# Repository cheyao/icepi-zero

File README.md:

# Icepi Zero - The portable FPGA development board

| Get your own at: | [**Crowd Supply**](https://www.crowdsupply.com/icy-electronics/icepi-zero) | [**Elecrow**](https://www.elecrow.com/icepi-zero.html) | [**Mouser Electronics**](https://eu.mouser.com/en/ProductDetail/Icy-Electronics/ICEPI-ZERO-QTY-1) |
| ---------------- | ------------------------ | ------------------ | --------- |

If you are a student/educational institute, send me an email at `cyao _at_ duck.com` and get a discount to buy an Icepi Zero at just $65 (shipping exclusive).

We also got a [Discord server](https://discord.gg/vzrqfhcvWr)! Feel free to ask any questions here.

## What is the Icepi Zero?

The Icepi Zero is an FPGA development board in the popular Raspberry Pi Zero form factor. It carries a Lattice ECP5 25F, enabling powerful designs while keeping a small portable size. It also has a GPDI mini (General Purpose Display Interface, same as the one on the Pi Zero) port allowing easy digital video output.

## Why Icepi Zero?

Currently most powerful FPGA boards on the market are expensive and bulky.

I've always wanted a low-cost portable FPGA with video output to make my own CPU, but there isn't any on the market.

The Icepi Zero aims to fix this. Carrying a powerful ECP5 FPGA on a small Raspberry Pi Zero form factor, it is the ultimate portable solution for FPGA development. Additionally packing a GPDI mini port and 3 USB-C ports, it allows interfacing with multiple external I/O devices.

Icepi Zero is for everyone: Students can use it to learn about the internals of modern processors. Gamers can use it to emulate old hardware. Programmers can use it to test their code on multiple architectures.

<sub>Oberon running on Icepi Zero</sub>

Icepi Zero also has an on-board USB to JTAG converter, so no external programmers are needed.

Moreover Icepi Zero is fully open-source, no strings attached. Learn from the design! ([OSHWA cerified FR000026](https://certification.oshwa.org/fr000026.html)).

## Features

- Raspberry Pi Zero form factor
- Lattice ECP5U FPGA:
    - 24k LUT
    - 112 KiB of RAM
- One MiniGPDI connector (it's HDM- but I don't have the money to buy a license...)
- Three USB-C Ports
- 256Mbit 166MHz SDRAM
- MicroSD card slot
- On-board USB to JTAG and UART converter
- 50MHz external oscillator
- 128 Mbit of flash
- 4 user LEDs
- 2 user buttons

This powerful configuration allows the PCB to be used in numerous ways, including real time video processing, hardware AI acceleration and prototyping of ASICs. 

## Emulation

Over the course of multiple weeks, multiple emulation cores have been ported over, such as the [Oberon](https://github.com/cheyao/oberon), [Apple I](https://github.com/cheyao/apple-one) and the [Acorn Atom](https://github.com/cheyao/acorn_atom)! The Icepi Zero allows you to take cycle accurate replicas of your favourite systems in your pocket.

<sub>Apple I running on the Icepi</sub>

<sub>Acorn Atom running on the Icepi</sub>

## Learning

It is also supported by icestudio (custom fork: https://github.com/cheyao/icestudio), allowing easy access for beginners.

## Usage

Check out the `gateware` folder for example code and compilation instructions!

If you want to order this board, it uses a 1.2mm/1.6mm PCB with JLC04121H-7628 Stackup. Gerbers are in the `production` folder in the `hardware` directory.

For the PCB, the smallest component size is 0201 for 27 Ohm resistors on the USB-C datalines. But if you want only 0402 components, just delete those 0201 resistors and you will be fine.

NOTE: If you fabbed v1.1 before 01/06, the pins of the USB pullups and LED0 is different - check your gerbers.

[View PCB online](https://kicanvas.org/?github=https%3A%2F%2Fgithub.com%2Fcheyao%2Ficepi-zero%2Ftree%2Fmain%2Fhardware%2Fv1.2)

## Acknowledgments

This project was inspired by the [ulx3s](https://github.com/emard/ulx3s), huge props to the ulx3s team for making such a good board!

## Contact

If there is any questions DM `cyao.` or join the [discord server](https://discord.gg/vzrqfhcvWr)! Feel free to ask any questions here. Mail is also accepted at `cyao _at_ duck.com`. :)

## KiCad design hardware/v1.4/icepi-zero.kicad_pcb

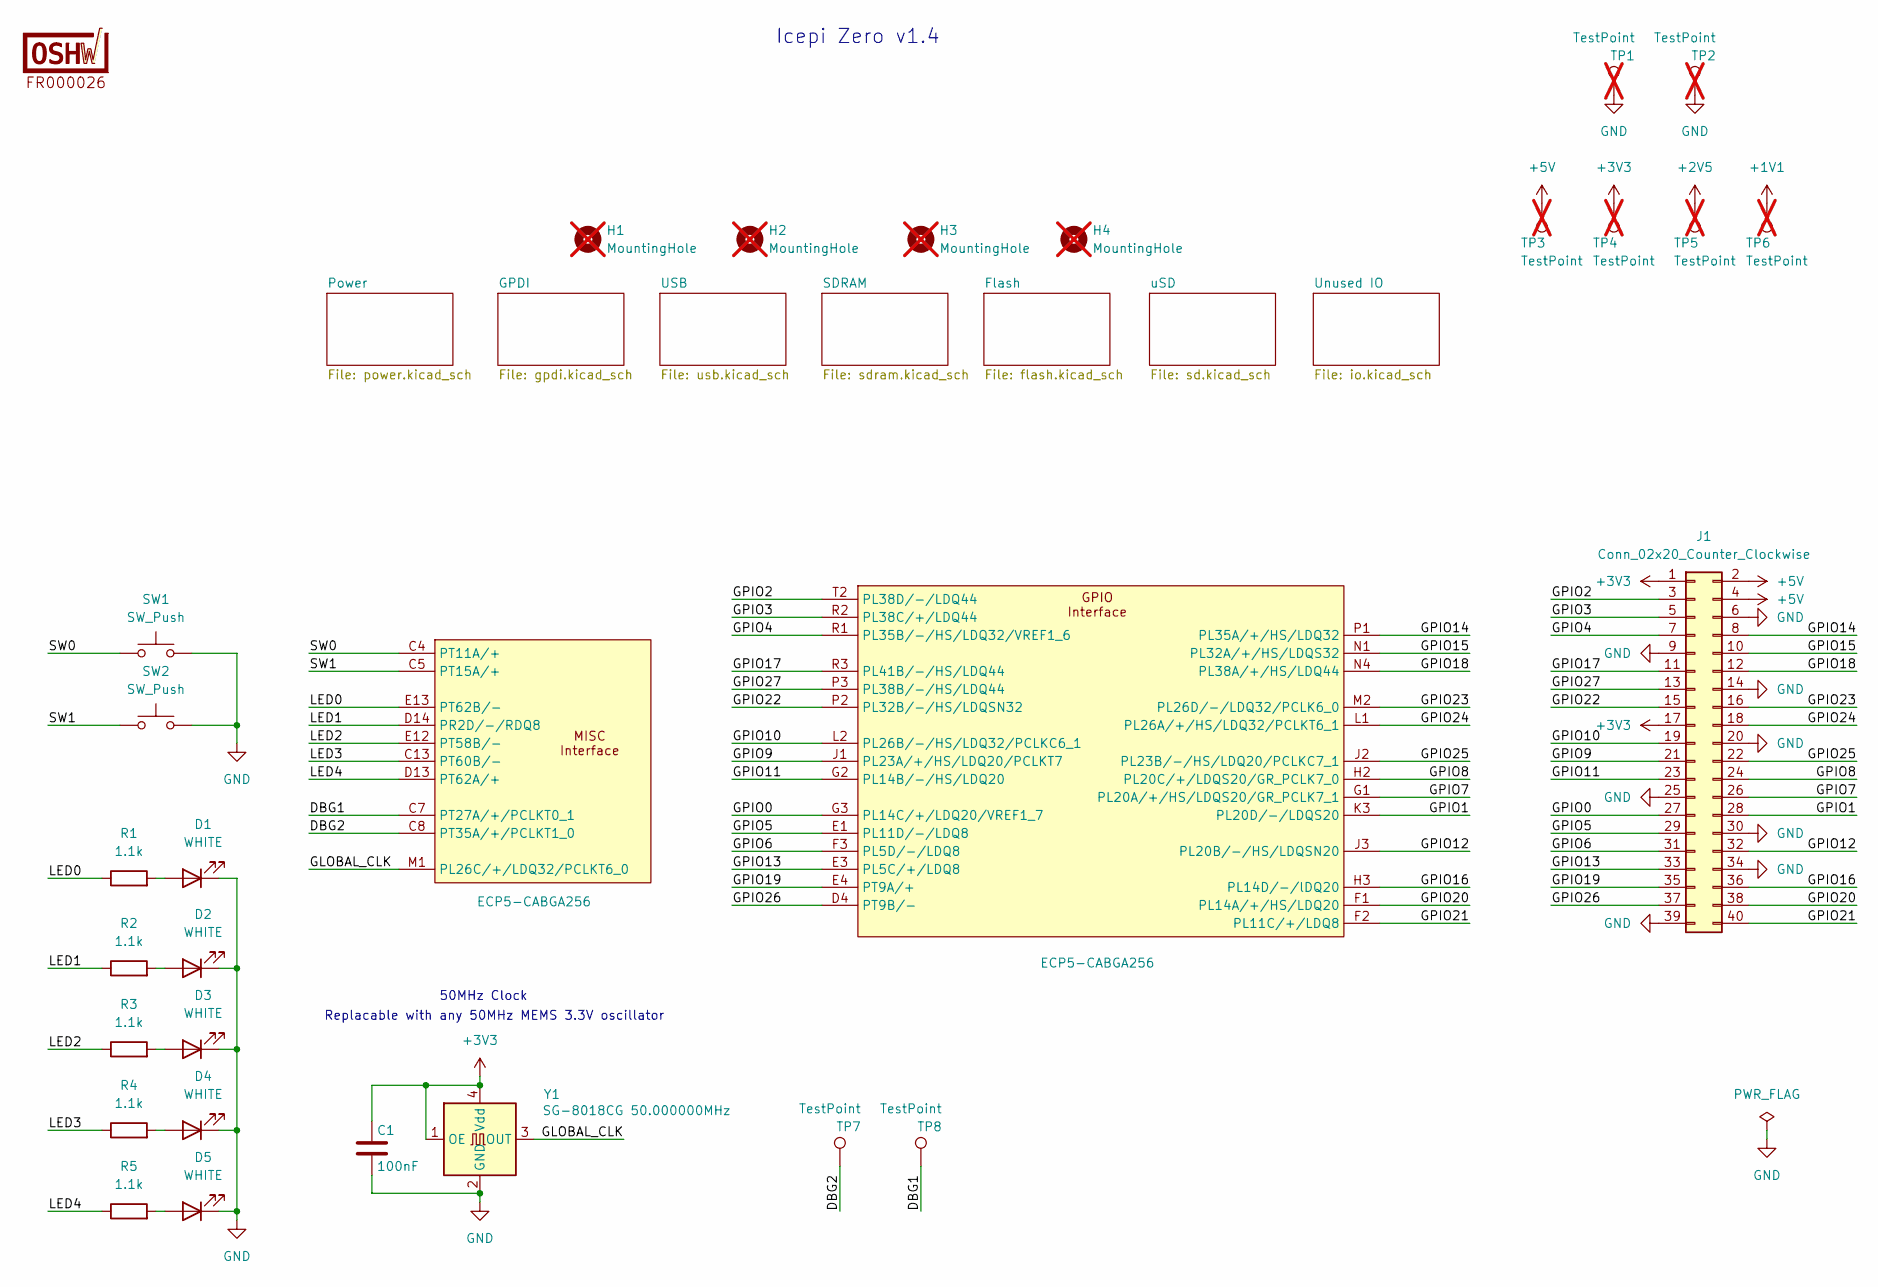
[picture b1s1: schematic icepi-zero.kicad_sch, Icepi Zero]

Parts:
C1: 100nF; C_0402_1005Metric; Manufactuer Part Number CL05B104KB54PNC; LCSC Part # C307331
D1, D2, D3, D4, D5: WHITE; LED_0603_1608Metric; Manufactuer Part Number KT-0603W; LCSC Part # C2290
H1, H2, H3, H4: MountingHole; MountingHole_2.7mm_M2.5; not fitted
J1: Conn_02x20_Counter_Clockwise; PinHeader_2x20_P2.54mm_Vertical
LOGO1: Icy Electronics Logo
R1, R2, R3, R4, R5: 1.1k; R_0402_1005Metric; Manufactuer Part Number 0402WGF1001TCE; LCSC Part # C140223
SW1, SW2: SW_Push; switch_button_TS-1088-AR02016; Manufactuer Part Number TS-1088-AR02016; LCSC Part # C720477
TP1, TP2, TP3, TP4, TP5, TP6: TestPoint; TestPoint_Pad_D2.0mm_Blank; not fitted
TP7, TP8: TestPoint; TestPoint_Pad_D1.0mm_Blank
U1: ECP5-CABGA256; BGA-256_14.0x14.0mm_Layout16x16_P0.8mm_Ball0.45mm_Pad0.32mm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; Manufactuer Part Number LFE5U-25F-6BG256C; LCSC Part # C1521614
Y1: SG-8018CG 50.000000MHz; Oscillator_SMD_SiT_PQFN-4Pin_2.5x2.0mm; Manufactuer Part Number SG-8018CG 50.000000MHz TJHSA; LCSC Part # C390526

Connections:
+1V1: TP6.1 (1_1); also elsewhere on the board
+2V5: TP5.1 (1_1); also elsewhere on the board
+3V3: C1.1, J1.1, J1.17, TP4.1 (1_1), Y1.1 (OE), Y1.4 (Vdd); also elsewhere on the board
+5V: J1.2, J1.4, TP3.1 (1_1); also elsewhere on the board
/DBG1: TP8.1 (1_1), U1.C7 (PT27A/+/PCLKT0_1)
/DBG2: TP7.1 (1_1), U1.C8 (PT35A/+/PCLKT1_0)
/GLOBAL_CLK: U1.M1 (PL26C/+/LDQ32/PCLKT6_0), Y1.3 (OUT)
/GPIO0: J1.27, U1.G3 (PL14C/+/LDQ20/VREF1_7)
/GPIO1: J1.28, U1.K3 (PL20D/-/LDQS20)
/GPIO2: J1.3, U1.T2 (PL38D/-/LDQ44)
/GPIO3: J1.5, U1.R2 (PL38C/+/LDQ44)
/GPIO4: J1.7, U1.R1 (PL35B/-/HS/LDQ32/VREF1_6)
/GPIO5: J1.29, U1.E1 (PL11D/-/LDQ8)
/GPIO6: J1.31, U1.F3 (PL5D/-/LDQ8)
/GPIO7: J1.26, U1.G1 (PL20A/+/HS/LDQS20/GR_PCLK7_1)
/GPIO8: J1.24, U1.H2 (PL20C/+/LDQS20/GR_PCLK7_0)
/GPIO9: J1.21, U1.J1 (PL23A/+/HS/LDQ20/PCLKT7)
/GPIO10: J1.19, U1.L2 (PL26B/-/HS/LDQ32/PCLKC6_1)
/GPIO11: J1.23, U1.G2 (PL14B/-/HS/LDQ20)
/GPIO12: J1.32, U1.J3 (PL20B/-/HS/LDQSN20)
/GPIO13: J1.33, U1.E3 (PL5C/+/LDQ8)
/GPIO14: J1.8, U1.P1 (PL35A/+/HS/LDQ32)
/GPIO15: J1.10, U1.N1 (PL32A/+/HS/LDQS32)
/GPIO16: J1.36, U1.H3 (PL14D/-/lDQ20)
/GPIO17: J1.11, U1.R3 (PL41B/-/HS/LDQ44)
/GPIO18: J1.12, U1.N4 (PL38A/+/HS/LDQ44)
/GPIO19: J1.35, U1.E4 (PT9A/+)
/GPIO20: J1.38, U1.F1 (PL14A/+/HS/LDQ20)
/GPIO21: J1.40, U1.F2 (PL11C/+/LDQ8)
/GPIO22: J1.15, U1.P2 (PL32B/-/HS/LDQSN32)
/GPIO23: J1.16, U1.M2 (PL26D/-/LDQ32/PCLK6_0)
/GPIO24: J1.18, U1.L1 (PL26A/+/HS/LDQ32/PCLKT6_1)
/GPIO25: J1.22, U1.J2 (PL23B/-/HS/LDQ20/PCLKC7_1)
/GPIO26: J1.37, U1.D4 (PT9B/-)
/GPIO27: J1.13, U1.P3 (PL38B/-/HS/LDQ44)
/LED0: R1.1, U1.E13 (PT62B/-)
/LED1: R2.1, U1.D14 (PR2D/-/RDQ8)
/LED2: R3.1, U1.E12 (PT58B/-)
/LED3: R4.1, U1.C13 (PT60B/-)
/LED4: R5.1, U1.D13 (PT62A/+)
/SW0: SW1.1, U1.C4 (PT11A/+)
/SW1: SW2.1, U1.C5 (PT15A/+)
GND: C1.2, D1.1 (K), D2.1 (K), D3.1 (K), D4.1 (K), D5.1 (K), J1.6, J1.9, J1.14, J1.20, J1.25, J1.30, J1.34, J1.39, SW1.2, SW2.2, TP1.1 (1_1), TP2.1 (1_1), Y1.2 (GND); also elsewhere on the board
unnamed: D1.2 (A), R1.2
unnamed: D2.2 (A), R2.2
unnamed: D3.2 (A), R3.2
unnamed: D4.2 (A), R4.2
unnamed: D5.2 (A), R5.2

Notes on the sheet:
Icepi Zero v1.4
Replacable with any 50MHz MEMS 3.3V oscillator
50MHz Clock

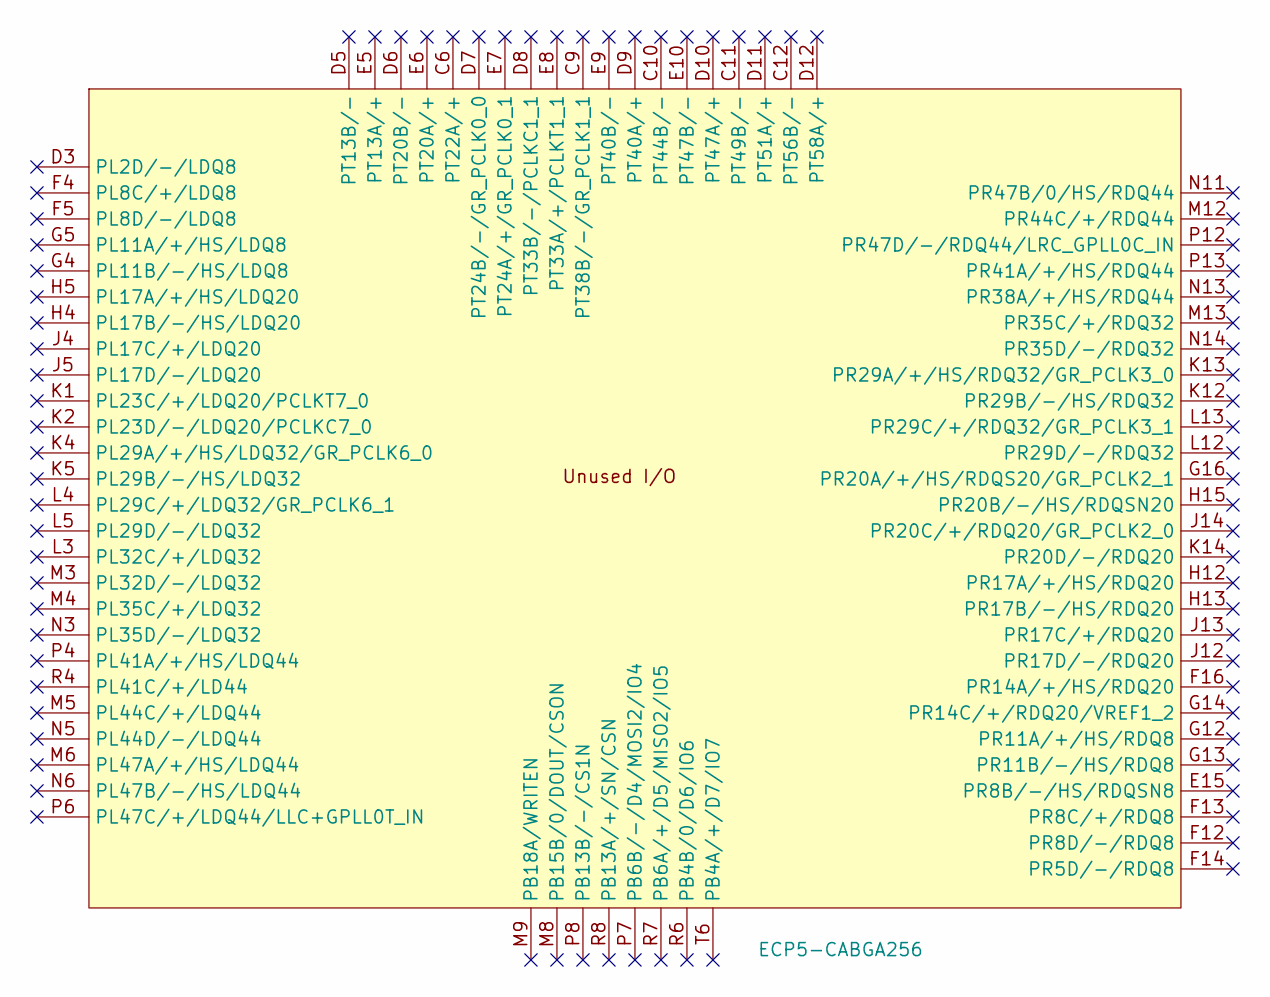
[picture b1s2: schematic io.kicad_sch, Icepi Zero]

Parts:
U1: ECP5-CABGA256; BGA-256_14.0x14.0mm_Layout16x16_P0.8mm_Ball0.45mm_Pad0.32mm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; Manufactuer Part Number LFE5U-25F-6BG256C; LCSC Part # C1521614

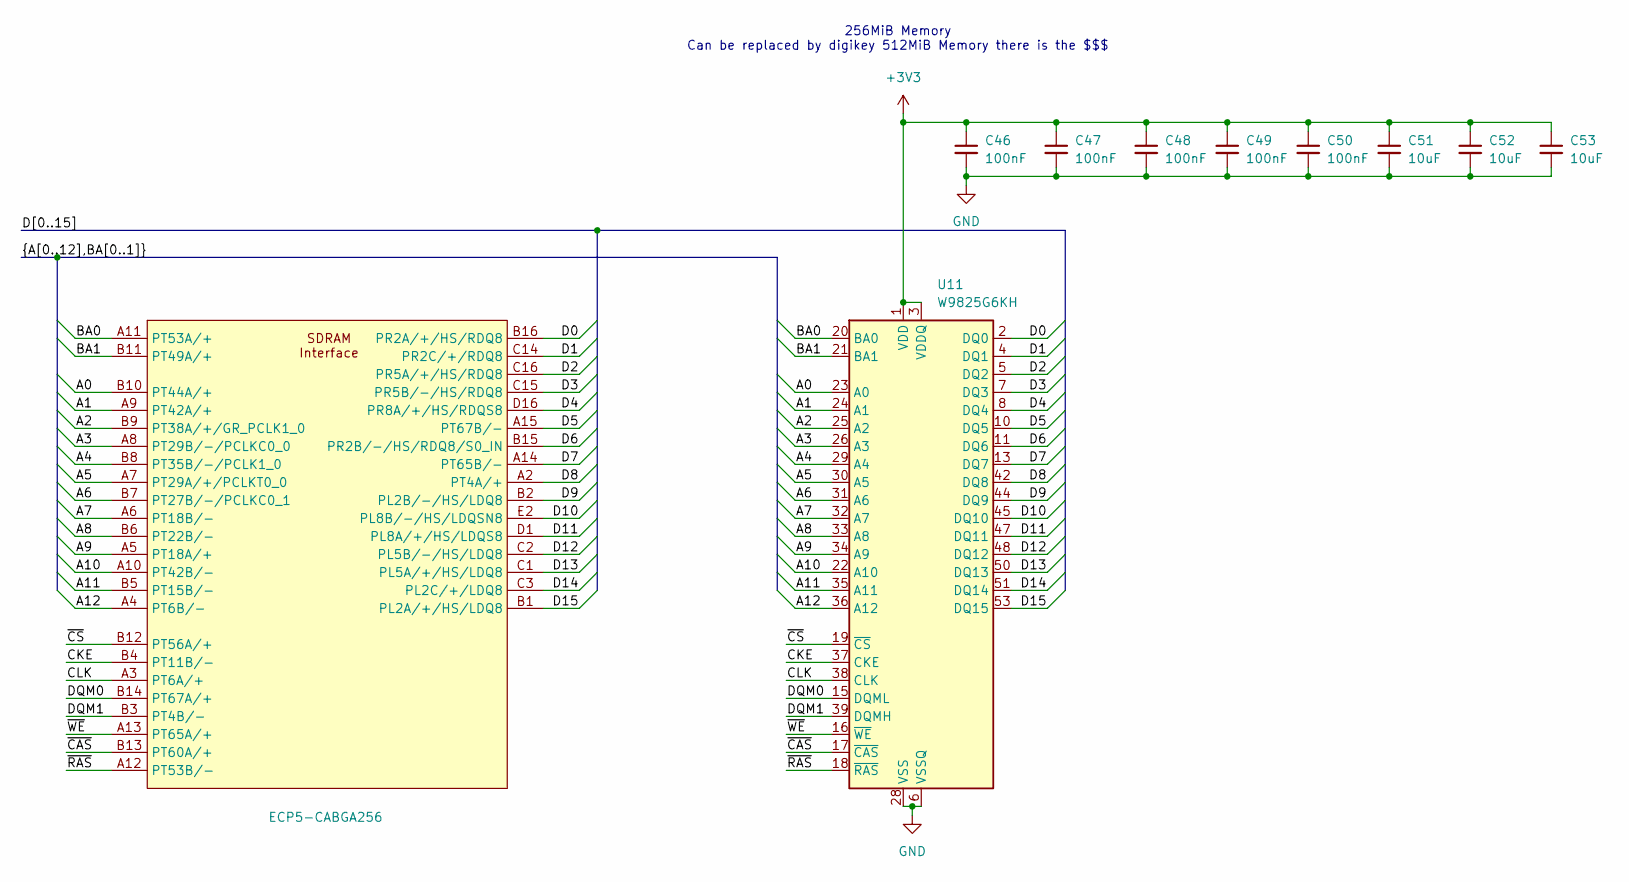
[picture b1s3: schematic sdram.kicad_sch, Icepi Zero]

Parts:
C46, C47, C48, C49, C50: 100nF; C_0402_1005Metric; Manufactuer Part Number CL05B104KB54PNC; LCSC Part # C307331
C51, C52, C53: 10uF; C_0603_1608Metric; Manufactuer Part Number CL10A106KP8NNNC; LCSC Part # C19702
U1: ECP5-CABGA256; BGA-256_14.0x14.0mm_Layout16x16_P0.8mm_Ball0.45mm_Pad0.32mm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; Manufactuer Part Number LFE5U-25F-6BG256C; LCSC Part # C1521614
U11: W9825G6KH; TSOP-II-54_22.2x10.16mm_P0.8mm; Manufactuer Part Number W9825G6KH-6; LCSC Part # C62246

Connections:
+3V3: C46.1, C47.1, C48.1, C49.1, C50.1, C51.1, C52.1, C53.1, U11.1 (VDD), U11.3 (VDDQ), U11.9 (VDDQ), U11.14 (VDD), U11.27 (VDD), U11.43 (VDDQ), U11.49 (VDDQ); also elsewhere on the board
/SDRAM/A0: U1.B10 (PT44A/+), U11.23 (A0)
/SDRAM/A1: U1.A9 (PT42A/+), U11.24 (A1)
/SDRAM/A2: U1.B9 (PT38A/+/GR_PCLK1_0), U11.25 (A2)
/SDRAM/A3: U1.A8 (PT29B/-/PCLKC0_0), U11.26 (A3)
/SDRAM/A4: U1.B8 (PT35B/-/PCLK1_0), U11.29 (A4)
/SDRAM/A5: U1.A7 (PT29A/+/PCLKT0_0), U11.30 (A5)
/SDRAM/A6: U1.B7 (PT27B/-/PCLKC0_1), U11.31 (A6)
/SDRAM/A7: U1.A6 (PT18B/-), U11.32 (A7)
/SDRAM/A8: U1.B6 (PT22B/-), U11.33 (A8)
/SDRAM/A9: U1.A5 (PT18A/+), U11.34 (A9)
/SDRAM/A10: U1.A10 (PT42B/-), U11.22 (A10)
/SDRAM/A11: U1.B5 (PT15B/-), U11.35 (A11)
/SDRAM/A12: U1.A4 (PT6B/-), U11.36 (A12)
/SDRAM/BA0: U1.A11 (PT53A/+), U11.20 (BA0)
/SDRAM/BA1: U1.B11 (PT49A/+), U11.21 (BA1)
/SDRAM/CKE: U1.B4 (PT11B/-), U11.37 (CKE)
/SDRAM/CLK: U1.A3 (PT6A/+), U11.38 (CLK)
/SDRAM/D0: U1.B16 (PR2A/+/HS/RDQ8), U11.2 (DQ0)
/SDRAM/D1: U1.C14 (PR2C/+/RDQ8), U11.4 (DQ1)
/SDRAM/D2: U1.C16 (PR5A/+/HS/RDQ8), U11.5 (DQ2)
/SDRAM/D3: U1.C15 (PR5B/-/HS/RDQ8), U11.7 (DQ3)
/SDRAM/D4: U1.D16 (PR8A/+/HS/RDQS8), U11.8 (DQ4)
/SDRAM/D5: U1.A15 (PT67B/-), U11.10 (DQ5)
/SDRAM/D6: U1.B15 (PR2B/-/HS/RDQ8/S0_IN), U11.11 (DQ6)
/SDRAM/D7: U1.A14 (PT65B/-), U11.13 (DQ7)
/SDRAM/D8: U1.A2 (PT4A/+), U11.42 (DQ8)
/SDRAM/D9: U1.B2 (PL2B/-/HS/LDQ8), U11.44 (DQ9)
/SDRAM/D10: U1.E2 (PL8B/-/HS/LDQSN8), U11.45 (DQ10)
/SDRAM/D11: U1.D1 (PL8A/+/HS/LDQS8), U11.47 (DQ11)
/SDRAM/D12: U1.C2 (PL5B/-/HS/LDQ8), U11.48 (DQ12)
/SDRAM/D13: U1.C1 (PL5A/+/HS/LDQ8), U11.50 (DQ13)
/SDRAM/D14: U1.C3 (PL2C/+/LDQ8), U11.51 (DQ14)
/SDRAM/D15: U1.B1 (PL2A/+/HS/LDQ8), U11.53 (DQ15)
/SDRAM/DQM0: U1.B14 (PT67A/+), U11.15 (DQML)
/SDRAM/DQM1: U1.B3 (PT4B/-), U11.39 (DQMH)
/SDRAM/~CAS: U1.B13 (PT60A/+), U11.17 (~CAS)
/SDRAM/~CS: U1.B12 (PT56A/+), U11.19 (~CS)
/SDRAM/~RAS: U1.A12 (PT53B/-), U11.18 (~RAS)
/SDRAM/~WE: U1.A13 (PT65A/+), U11.16 (~WE)
GND: C46.2, C47.2, C48.2, C49.2, C50.2, C51.2, C52.2, C53.2, U11.6 (VSSQ), U11.12 (VSSQ), U11.28 (VSS), U11.41 (VSS), U11.46 (VSSQ), U11.52 (VSSQ), U11.54 (VSS); also elsewhere on the board

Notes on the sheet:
256MiB Memory Can be replaced by digikey 512MiB Memory there is the $$$

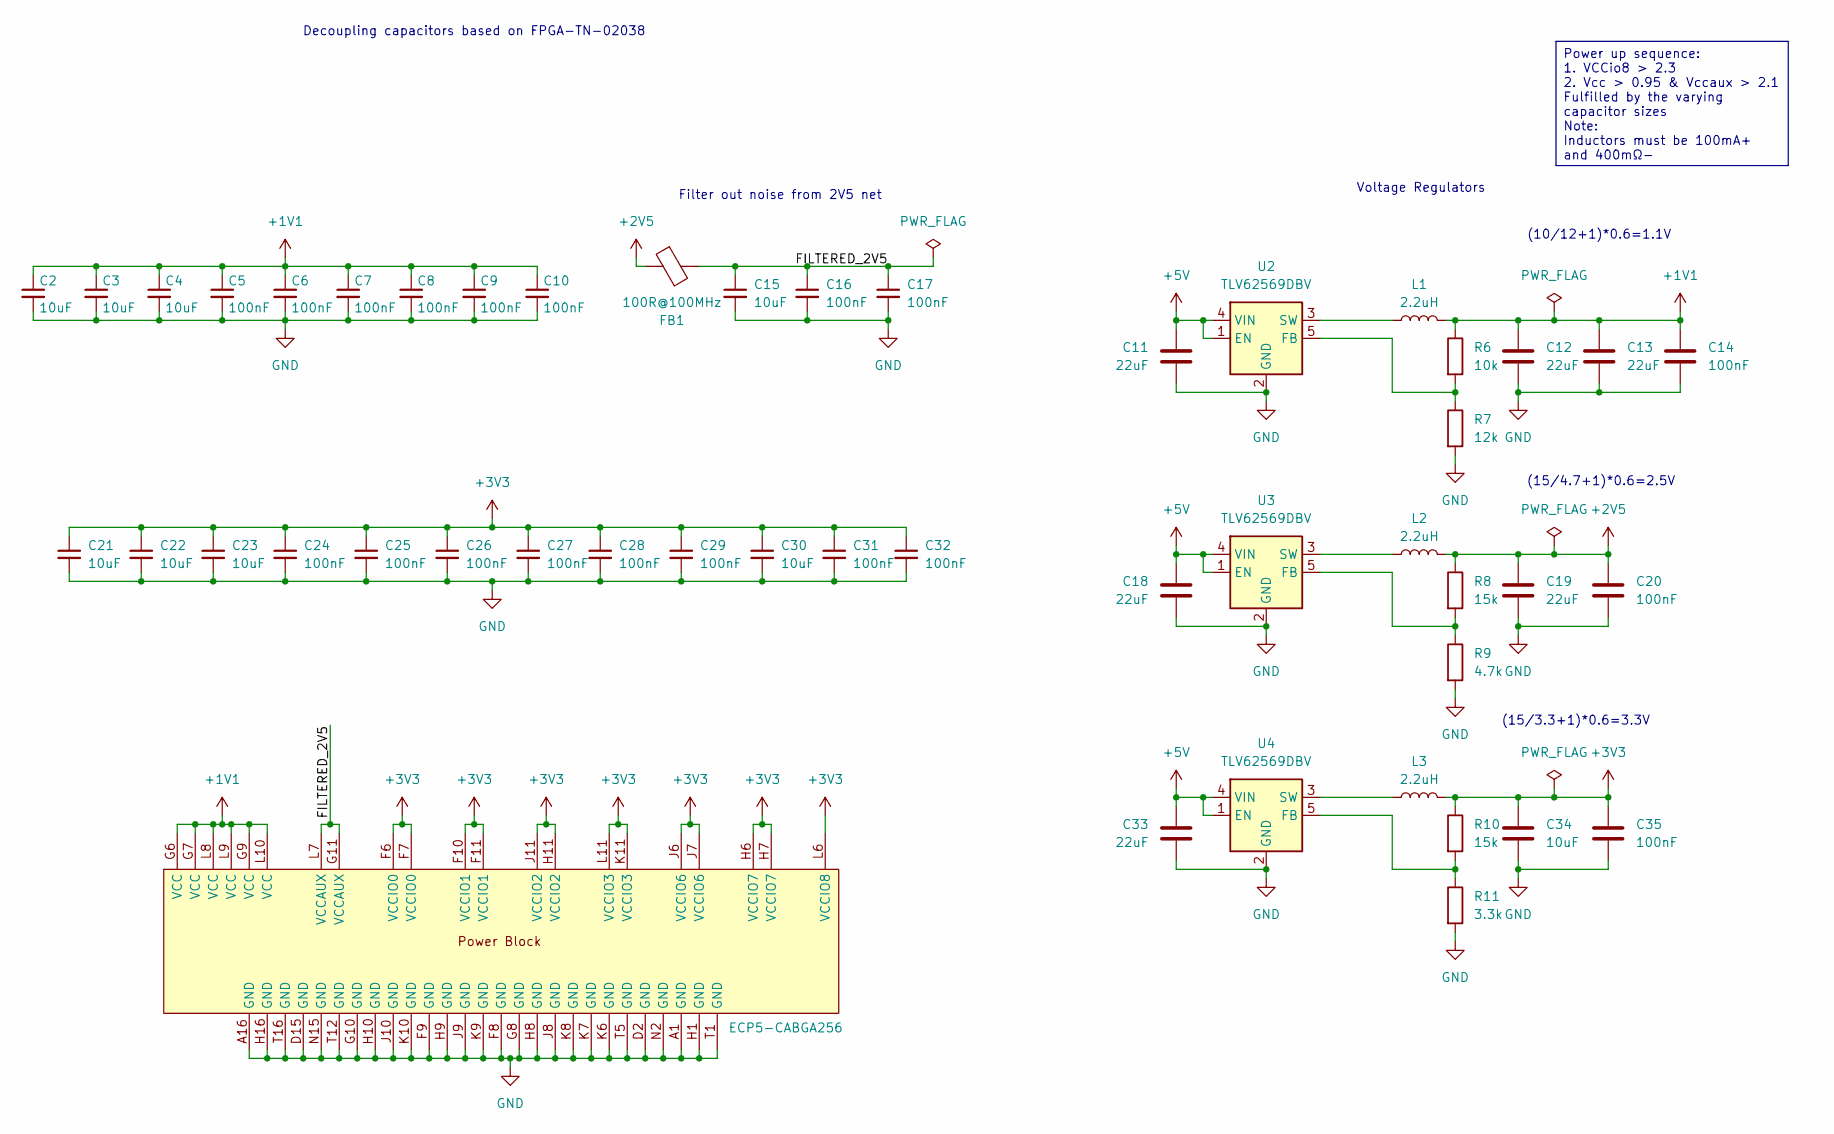
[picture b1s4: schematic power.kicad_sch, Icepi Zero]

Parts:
C2, C3, C4, C15, C21, C22, C23, C30, C34: 10uF; C_0603_1608Metric; Manufactuer Part Number CL10A106KP8NNNC; LCSC Part # C19702
C5, C6, C7, C8, C9, C10, C14, C16, C17, C20, C24, C25, C26, C27, C28, C29, C31, C32, C35: 100nF; C_0402_1005Metric; Manufactuer Part Number CL05B104KB54PNC; LCSC Part # C307331
C11, C12, C13, C18, C19, C33: 22uF; C_0603_1608Metric; Manufactuer Part Number CL10A226MQ8NRNC; LCSC Part # C59461
FB1: 100R@100MHz; L_0805_2012Metric; Manufactuer Part Number CBG201209U101T; LCSC Part # C74480
L1, L2, L3: 2.2uH; L_0805_2012Metric; Manufactuer Part Number TDK MLP2012S2R2MT0S1; LCSC Part # C107322
R6: 10k; R_0402_1005Metric; Manufactuer Part Number 0402WGF1002TCE; LCSC Part # C25744
R7: 12k; R_0402_1005Metric; Manufactuer Part Number 0402WGF1202TCE; LCSC Part # C25752
R8, R10: 15k; R_0402_1005Metric; Manufactuer Part Number 0402WGF1502TCE; LCSC Part # C25756
R9: 4.7k; R_0402_1005Metric; Manufactuer Part Number 0402WGF4701TCE; LCSC Part # C25900
R11: 3.3k; R_0402_1005Metric; Manufactuer Part Number 0402WGF3301TCE; LCSC Part # C25890
U1: ECP5-CABGA256; BGA-256_14.0x14.0mm_Layout16x16_P0.8mm_Ball0.45mm_Pad0.32mm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; Manufactuer Part Number LFE5U-25F-6BG256C; LCSC Part # C1521614
U2, U3, U4: TLV62569DBV; SOT-23-5; Manufactuer Part Number TLV62569DBVR; LCSC Part # C141836

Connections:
+1V1: C2.1, C3.1, C4.1, C5.1, C6.1, C7.1, C8.1, C9.1, C10.1, C12.1, C13.1, C14.1, L1.2, R6.1, U1.G6 (VCC), U1.G7 (VCC), U1.G9 (VCC), U1.L8 (VCC), U1.L9 (VCC), U1.L10 (VCC); also elsewhere on the board
+2V5: C19.1, C20.1, FB1.1, L2.2, R8.1; also elsewhere on the board
+3V3: C21.1, C22.1, C23.1, C24.1, C25.1, C26.1, C27.1, C28.1, C29.1, C30.1, C31.1, C32.1, C34.1, C35.1, L3.2, R10.1, U1.F6 (VCCIO0), U1.F7 (VCCIO0), U1.F10 (VCCIO1), U1.F11 (VCCIO1), U1.H6 (VCCIO7), U1.H7 (VCCIO7), U1.H11 (VCCIO2), U1.J6 (VCCIO6), U1.J7 (VCCIO6), U1.J11 (VCCIO2), U1.K11 (VCCIO3), U1.L6 (VCCIO8), U1.L11 (VCCIO3); also elsewhere on the board
+5V: C11.1, C18.1, C33.1, U2.1 (EN), U2.4 (VIN), U3.1 (EN), U3.4 (VIN), U4.1 (EN), U4.4 (VIN); also elsewhere on the board
/Power/FILTERED_2V5: C15.1, C16.1, C17.1, FB1.2, U1.G11 (VCCAUX), U1.L7 (VCCAUX)
GND: C2.2, C3.2, C4.2, C5.2, C6.2, C7.2, C8.2, C9.2, C10.2, C11.2, C12.2, C13.2, C14.2, C15.2, C16.2, C17.2, C18.2, C19.2, C20.2, C21.2, C22.2, C23.2, C24.2, C25.2, C26.2, C27.2, C28.2, C29.2, C30.2, C31.2, C32.2, C33.2, C34.2, C35.2, R7.2, R9.2, R11.2, U1.A1 (GND), U1.A16 (GND), U1.D2 (GND), U1.D15 (GND), U1.F8 (GND), U1.F9 (GND), U1.G8 (GND), U1.G10 (GND), U1.H1 (GND), U1.H8 (GND), U1.H9 (GND), U1.H10 (GND), U1.H16 (GND), U1.J8 (GND), U1.J9 (GND), U1.J10 (GND), U1.K6 (GND), U1.K7 (GND), U1.K8 (GND), U1.K9 (GND), U1.K10 (GND), U1.N2 (GND), U1.N15 (GND), U1.T1 (GND), U1.T5 (GND), U1.T12 (GND), U1.T16 (GND), U2.2 (GND), U3.2 (GND), U4.2 (GND); also elsewhere on the board
unnamed: R6.2, R7.1, U2.5 (FB)
unnamed: L1.1, U2.3 (SW)
unnamed: R8.2, R9.1, U3.5 (FB)
unnamed: L2.1, U3.3 (SW)
unnamed: R10.2, R11.1, U4.5 (FB)
unnamed: L3.1, U4.3 (SW)

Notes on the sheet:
Decoupling capacitors based on FPGA-TN-02038
(15/4.7+1)*0.6=2.5V
(10/12+1)*0.6=1.1V
Filter out noise from 2V5 net
(15/3.3+1)*0.6=3.3V
Voltage Regulators
Power up sequence: 1. VCCio8 > 2.3 2. Vcc > 0.95 & Vccaux > 2.1 Fulfilled by the varying capacitor sizes Note: Inductors must be 100mA+ and 400mΩ-

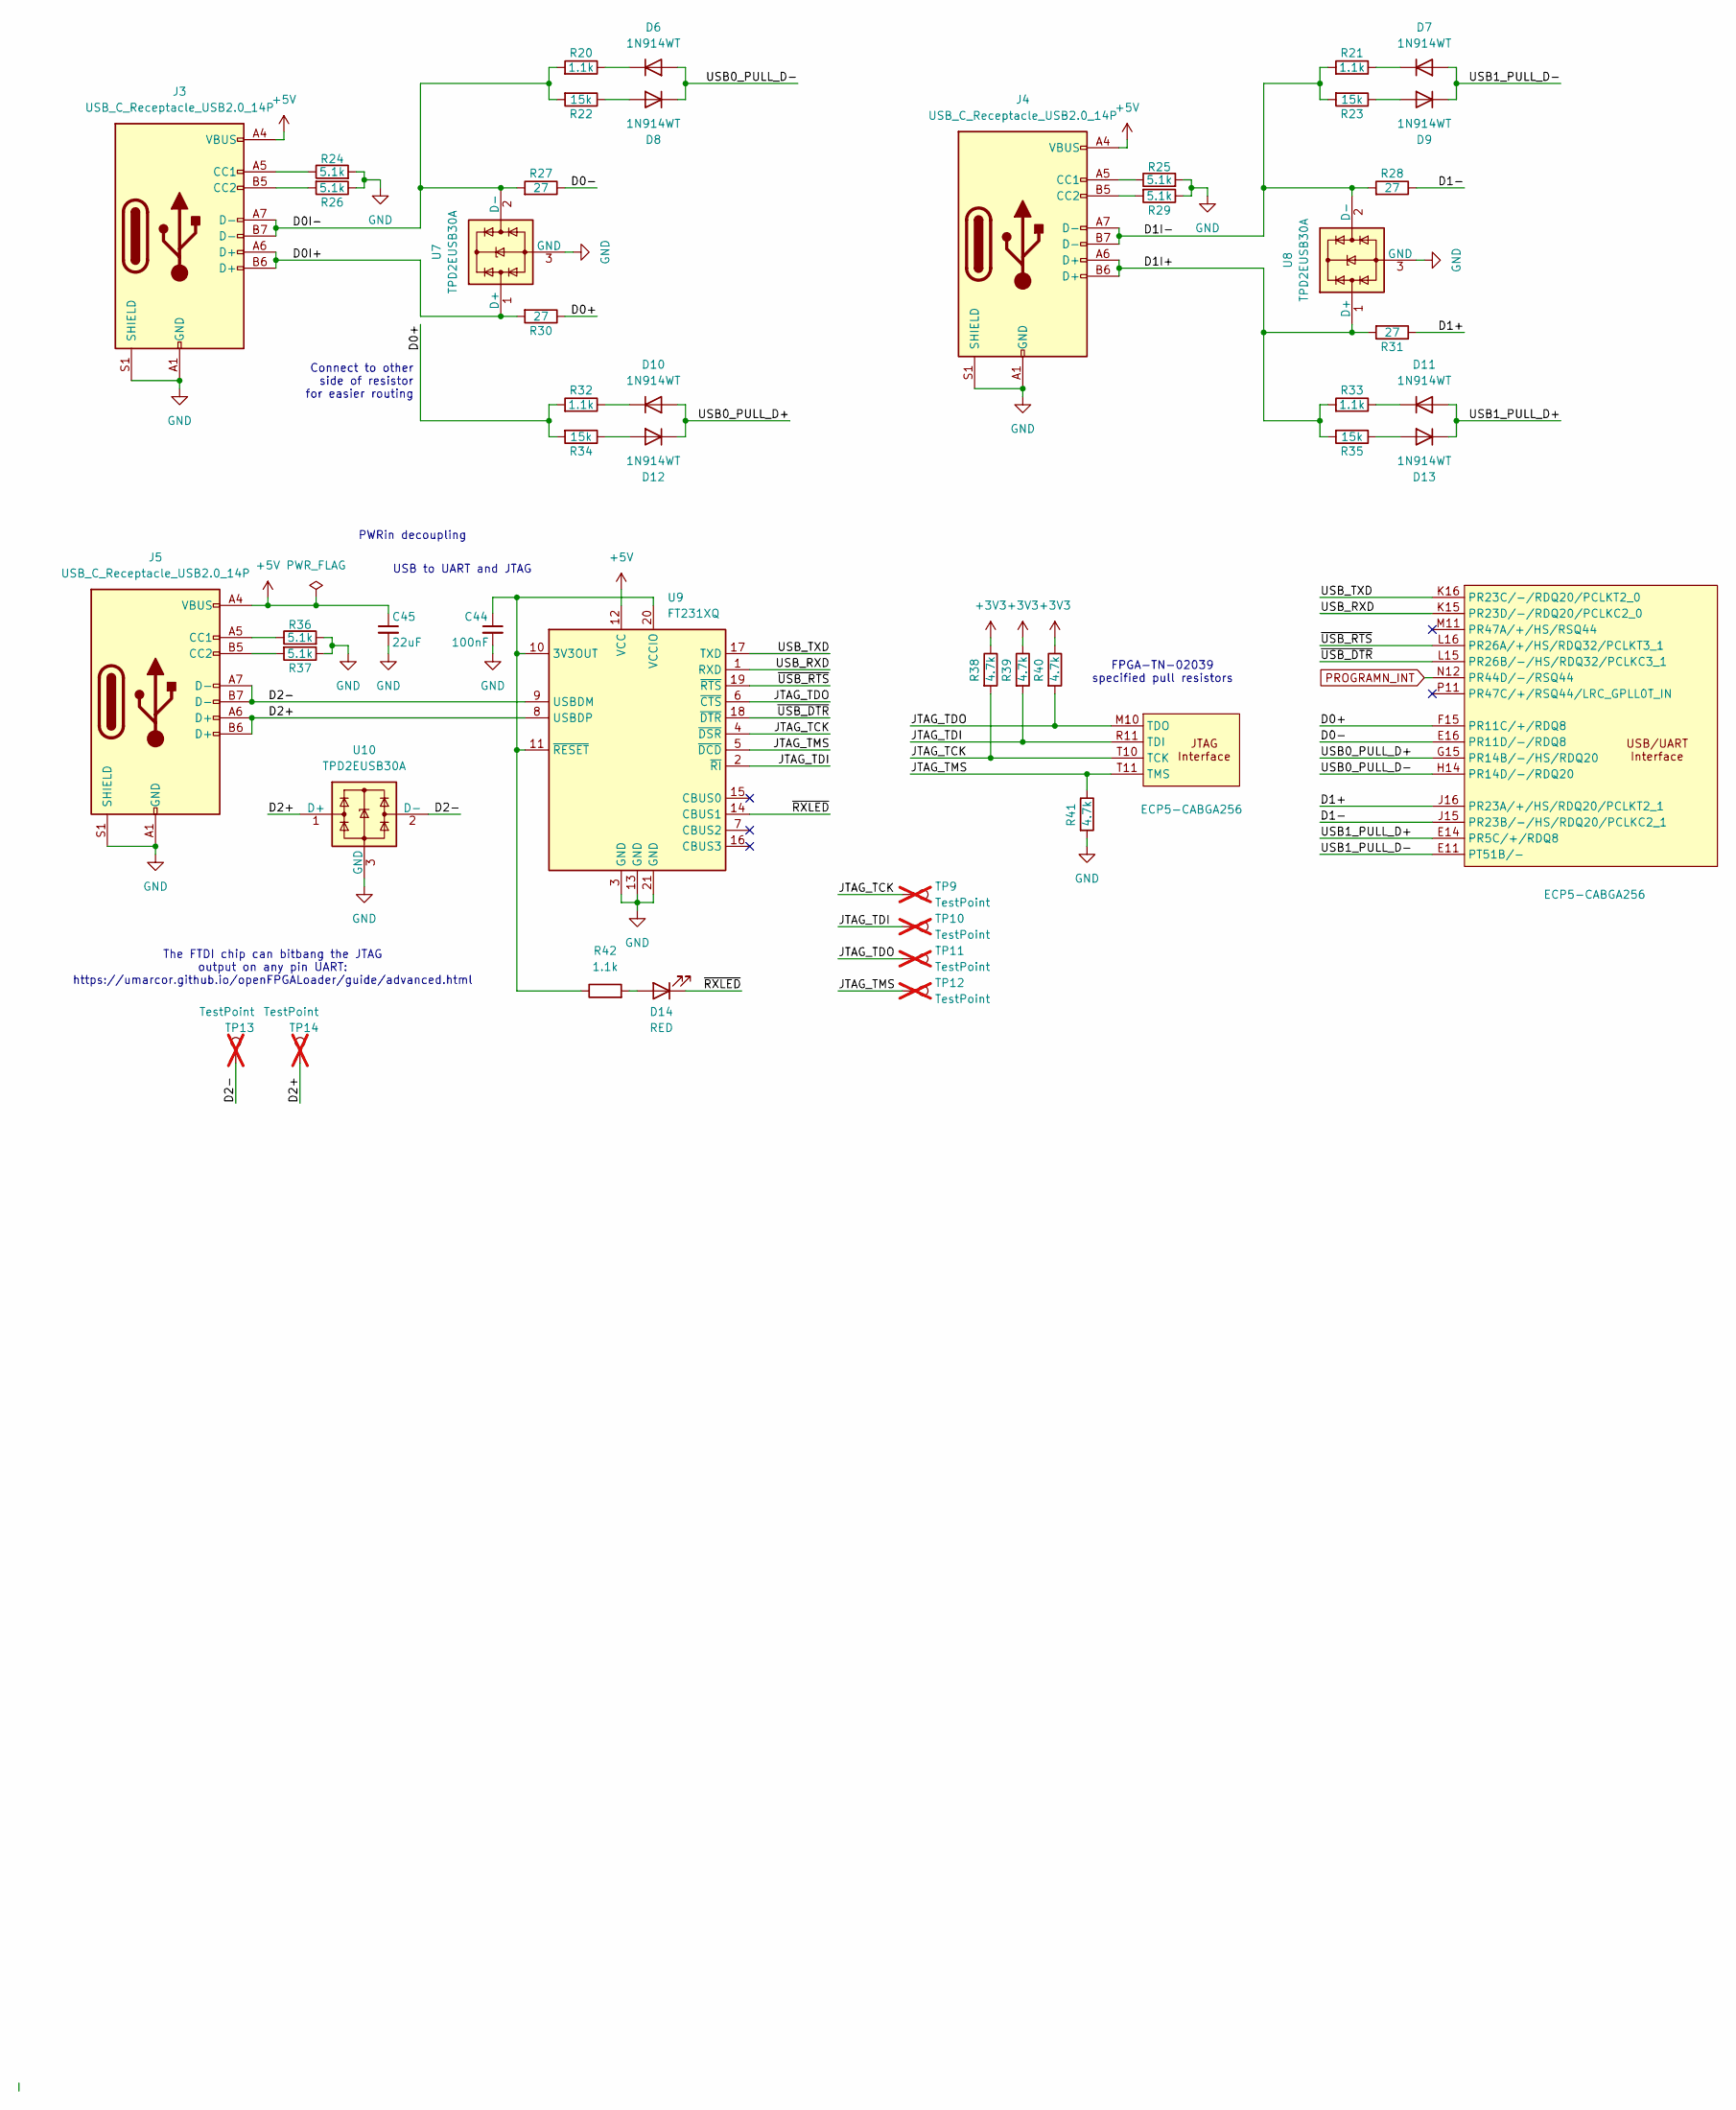
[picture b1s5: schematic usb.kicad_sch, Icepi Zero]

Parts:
C44: 100nF; C_0402_1005Metric; Manufactuer Part Number CL05B104KB54PNC; LCSC Part # C307331
C45: 22uF; C_0603_1608Metric; Manufactuer Part Number CL10A226MQ8NRNC; LCSC Part # C59461
D6, D7, D8, D9, D10, D11, D12, D13: 1N914WT; D_SOD-523; Manufactuer Part Number 1N914WT; LCSC Part # C2836064
D14: RED; LED_0603_1608Metric; Manufactuer Part Number KT-0603R; LCSC Part # C2286
J3, J4, J5: USB_C_Receptacle_USB2.0_14P; USB_C_Receptacle_GCT_USB4105-xx-A_16P_TopMnt_Horizontal; Manufactuer Part Number TYPE-C 16PIN 2MD(073); LCSC Part # C2765186
R20, R21, R32, R33, R42: 1.1k; R_0402_1005Metric; Manufactuer Part Number 0402WGF1001TCE; LCSC Part # C140223
R22, R23, R34, R35: 15k; R_0402_1005Metric; Manufactuer Part Number 0402WGF1502TCE; LCSC Part # C25756
R24, R25, R26, R29, R36, R37: 5.1k; R_0402_1005Metric; Manufactuer Part Number 0402WGF5101TCE; LCSC Part # C25905
R27, R28, R30, R31: 27; R_0201_0603Metric; Manufactuer Part Number 0201WMF270JTEE; LCSC Part # C473051
R38, R39, R40, R41: 4.7k; R_0402_1005Metric; Manufactuer Part Number 0402WGF4701TCE; LCSC Part # C25900
TP9, TP10, TP11, TP12: TestPoint; TestPoint_Pad_D1.0mm_Blank; not fitted
TP13, TP14: TestPoint; TestPoint_Pad_D2.0mm_Blank; not fitted
U1: ECP5-CABGA256; BGA-256_14.0x14.0mm_Layout16x16_P0.8mm_Ball0.45mm_Pad0.32mm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; Manufactuer Part Number LFE5U-25F-6BG256C; LCSC Part # C1521614
U7, U8, U10: TPD2EUSB30A; Texas_DRT-3; Manufactuer Part Number TPD2EUSB30ADRTR; LCSC Part # C3011197
U9: FT231XQ; QFN-20-1EP_4x4mm_P0.5mm_EP2.5x2.5mm; Manufactuer Part Number FT231XQ-R; LCSC Part # C132159

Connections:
+3V3: R38.1, R39.1, R40.1; also elsewhere on the board
+5V: C45.1, J3.A4 (VBUS), J3.A9 (VBUS), J3.B4 (VBUS), J3.B9 (VBUS), J4.A4 (VBUS), J4.A9 (VBUS), J4.B4 (VBUS), J4.B9 (VBUS), J5.A4 (VBUS), J5.A9 (VBUS), J5.B4 (VBUS), J5.B9 (VBUS), U9.12 (VCC); also elsewhere on the board
/USB/D0+: R30.1, R32.2, R34.2, U1.F15 (PR11C/+/RDQ8)
/USB/D0-: R27.1, U1.E16 (PR11D/-/RDQ8)
/USB/D0I+: J3.A6 (D+), J3.B6 (D+), R30.2, U7.1 (D+)
/USB/D0I-: J3.A7 (D-), J3.B7 (D-), R20.2, R22.2, R27.2, U7.2 (D-)
/USB/D1+: R31.1, U1.J16 (PR23A/+/HS/RDQ20/PCLKT2_1)
/USB/D1-: R28.1, U1.J15 (PR23B/-/HS/RDQ20/PCLKC2_1)
/USB/D1I+: J4.A6 (D+), J4.B6 (D+), R31.2, R33.2, R35.2, U8.1 (D+)
/USB/D1I-: J4.A7 (D-), J4.B7 (D-), R21.2, R23.2, R28.2, U8.2 (D-)
/USB/D2+: J5.A6 (D+), J5.B6 (D+), TP14.1 (1_1), U9.8 (USBDP), U10.1 (D+)
/USB/D2-: J5.A7 (D-), J5.B7 (D-), TP13.1 (1_1), U9.9 (USBDM), U10.2 (D-)
/USB/JTAG_TCK: R38.2, TP9.1 (1_1), U1.T10 (TCK), U9.4 (~DSR)
/USB/JTAG_TDI: R39.2, TP10.1 (1_1), U1.R11 (TDI), U9.2 (~RI)
/USB/JTAG_TDO: R40.2, TP11.1 (1_1), U1.M10 (TDO), U9.6 (~CTS)
/USB/JTAG_TMS: R41.1, TP12.1 (1_1), U1.T11 (TMS), U9.5 (~DCD)
/USB/USB0_PULL_D+: D10.2 (A), D12.1 (K), U1.G15 (PR14B/-/HS/RDQ20)
/USB/USB0_PULL_D-: D6.2 (A), D8.1 (K), U1.H14 (PR14D/-/RDQ20)
/USB/USB1_PULL_D+: D11.2 (A), D13.1 (K), U1.E14 (PR5C/+/RDQ8)
/USB/USB1_PULL_D-: D7.2 (A), D9.1 (K), U1.E11 (PT51B/-)
/USB/USB_RXD: U1.K15 (PR23D/-/RDQ20/PCLKC2_0), U9.1 (RXD)
/USB/USB_TXD: U1.K16 (PR23C/-/RDQ20/PCLKT2_0), U9.17 (TXD)
/USB/~RXLED: D14.1 (K), U9.14 (CBUS1)
/USB/~USB_DTR: U1.L15 (PR26B/-/HS/RDQ32/PCLKC3_1), U9.18 (~DTR)
/USB/~USB_RTS: U1.L16 (PR26A/+/HS/RDQ32/PCLKT3_1), U9.19 (~RTS)
GND: C44.2, C45.2, J3.A1 (GND), J3.A12 (GND), J3.B1 (GND), J3.B12 (GND), J3.S1 (SHIELD), J4.A1 (GND), J4.A12 (GND), J4.B1 (GND), J4.B12 (GND), J4.S1 (SHIELD), J5.A1 (GND), J5.A12 (GND), J5.B1 (GND), J5.B12 (GND), J5.S1 (SHIELD), R24.2, R25.2, R26.1, R29.1, R36.2, R37.1, R41.2, U7.3 (GND), U8.3 (GND), U9.3 (GND), U9.13 (GND), U9.21 (GND), U10.3 (GND); also elsewhere on the board
unnamed: D6.1 (K), R20.1
unnamed: D7.1 (K), R21.1
unnamed: D8.2 (A), R22.1
unnamed: D9.2 (A), R23.1
unnamed: D10.1 (K), R32.1
unnamed: D11.1 (K), R33.1
unnamed: D12.2 (A), R34.1
unnamed: D13.2 (A), R35.1
unnamed: D14.2 (A), R42.2
unnamed: J3.A5 (CC1), R24.1
unnamed: J3.B5 (CC2), R26.2
unnamed: J4.A5 (CC1), R25.1
unnamed: J4.B5 (CC2), R29.2
unnamed: J5.A5 (CC1), R36.1
unnamed: J5.B5 (CC2), R37.2
unnamed: C44.1, R42.1, U9.10 (3V3OUT), U9.11 (~RESET), U9.20 (VCCIO)
PROGRAMN_INT: U1.N12 (PR44D/-/RSQ44); also elsewhere on the board

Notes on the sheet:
PWRin decoupling
FPGA-TN-02039 specified pull resistors
USB to UART and JTAG
The FTDI chip can bitbang the JTAG output on any pin UART: https://umarcor.github.io/openFPGALoader/guide/advanced.html
Connect to other side of resistor for easier routing

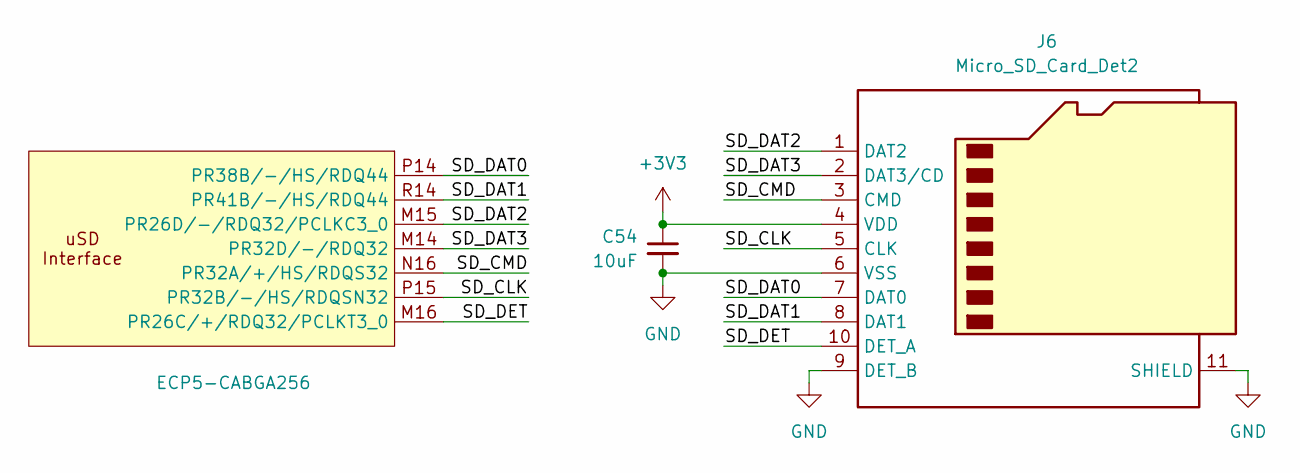
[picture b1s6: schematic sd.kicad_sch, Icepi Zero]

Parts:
C54: 10uF; C_0603_1608Metric; Manufactuer Part Number CL10A106KP8NNNC; LCSC Part # C19702
J6: Micro_SD_Card_Det2; microSD_HC_SOFNG_TF-008; Manufactuer Part Number TF-008; LCSC Part # C428465
U1: ECP5-CABGA256; BGA-256_14.0x14.0mm_Layout16x16_P0.8mm_Ball0.45mm_Pad0.32mm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; Manufactuer Part Number LFE5U-25F-6BG256C; LCSC Part # C1521614

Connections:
+3V3: C54.1, J6.4 (VDD); also elsewhere on the board
/uSD/SD_CLK: J6.5 (CLK), U1.P15 (PR32B/-/HS/RDQSN32)
/uSD/SD_CMD: J6.3 (CMD), U1.N16 (PR32A/+/HS/RDQS32)
/uSD/SD_DAT0: J6.7 (DAT0), U1.P14 (PR38B/-/HS/RDQ44)
/uSD/SD_DAT1: J6.8 (DAT1), U1.R14 (PR41B/-/HS/RDQ44)
/uSD/SD_DAT2: J6.1 (DAT2), U1.M15 (PR26D/-/RDQ32/PCLKC3_0)
/uSD/SD_DAT3: J6.2 (DAT3/CD), U1.M14 (PR32D/-/RDQ32)
/uSD/SD_DET: J6.10 (DET_A), U1.M16 (PR26C/+/RDQ32/PCLKT3_0)
GND: C54.2, J6.6 (VSS), J6.9 (DET_B), J6.11 (SHIELD); also elsewhere on the board

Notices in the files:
hardware/v1.4-wip/flash.kicad_sch:
License: Solderpad
